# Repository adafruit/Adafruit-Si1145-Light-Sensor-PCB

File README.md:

## Adafruit Si1145 Light Sensor PCB
<a href="http://www.adafruit.com/products/1777"><br/>
Click here to purchase one from the Adafruit shop</a>

The SI1145 is a new sensor from SiLabs with a calibrated light sensing algorithm that can calculate UV Index. It doesn't contain an actual UV sensing element, instead it approximates it based on visible & IR light from the sun. We took this outside a couple days and compared the calculated UV index with the news-reported index and found it was very accurate! It's a digital sensor that works over I2C so just about any microcontroller can use it. The sensor also has individual visible and IR sensing elements so you can measure just about any kind of light - we only wrote our library to printout the 'counts' rather than the calculate the exact values of IR and Visible light so if you need precision Lux measurement check out the TSL2561. If you're feeling really advanced, you can connect up an IR LED to the LED pin and use the basic proximity sensor capability that is in the SI1145 as well.

PCB files for the Adafruit Si1145 Light Sensor. The format is EagleCAD schematic and board layout
- https://www.adafruit.com/product/1777

### License

Adafruit invests time and resources providing this open source design, please support Adafruit and open-source hardware by purchasing products from [Adafruit](https://www.adafruit.com)!

All text above must be included in any redistribution

Designed by Limor Fried/Ladyada for Adafruit Industries.
Creative Commons Attribution/Share-Alike, all text above must be included in any redistribution. 
See license.txt for additional information.

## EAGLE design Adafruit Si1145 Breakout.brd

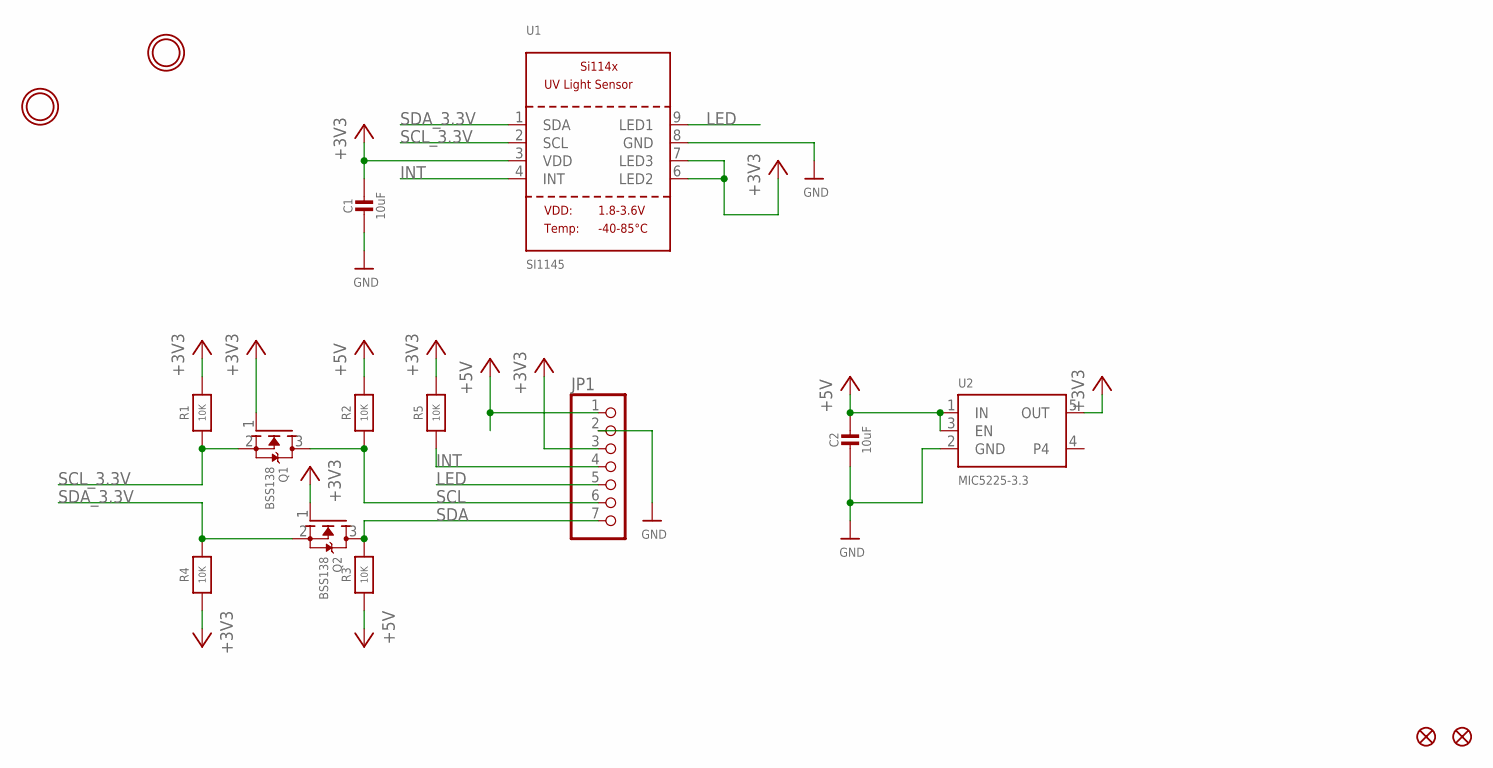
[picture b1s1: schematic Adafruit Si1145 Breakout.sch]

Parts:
C1, C2: 10uF; 0805-NO
FID1, FID2: FIDUCIAL""; FIDUCIAL_1MM
JP1: HEADER-1X770MIL; 1X07_ROUND_70
Q1, Q2: BSS138; SOT23-WIDE
R1, R2, R3, R4, R5: 10K; 0805-NO
U1: SI1145; SI114X
U2: MIC5225-3.3; SOT23-5
U$5, U$6: MOUNTINGHOLE2.5; MOUNTINGHOLE_2.5_PLATED

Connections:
+3V3: C1.1, JP1.3, Q1.1 (G), Q2.1 (G), R1.2, R4.1, R5.2, U1.3 (VDD), U1.6 (LED2), U1.7 (LED3), U2.5 (OUT)
GND: C1.2, C2.2, JP1.2, U1.8 (GND), U2.2 (GND)
INT: JP1.4, R5.1, U1.4 (INT)
LED: JP1.5, U1.9 (LED1)
SCL: JP1.6, Q1.3 (D), R2.1
SCL_3.3V: Q1.2 (S), R1.1, U1.2 (SCL)
SDA: JP1.7, Q2.3 (D), R3.2
SDA_3.3V: Q2.2 (S), R4.2, U1.1 (SDA)
VIN: C2.1, JP1.1, R2.2, R3.1, U2.1 (IN), U2.3 (EN)

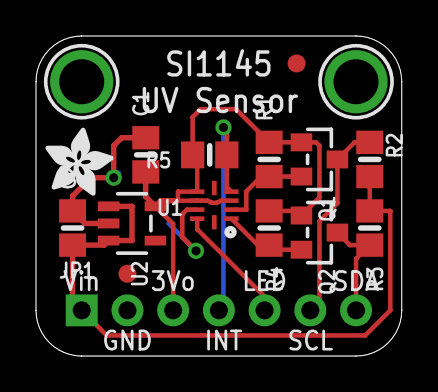
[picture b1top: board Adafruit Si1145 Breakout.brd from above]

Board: 2 copper layers, 20.3 x 17.8 mm, 18 parts (1 on the bottom side), 9 nets.

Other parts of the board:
U$3: ADAFRUIT_3.5MM
U$8: ADAFRUIT_5MM

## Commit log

2016-08-17 init

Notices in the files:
parts and their libraries:
microbuilder: This work is placed in the public domain, and may be freely used for commercial and non-commercial work with the following conditions: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
